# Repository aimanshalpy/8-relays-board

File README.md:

# 8 Relays Board
# 8 relays board with optocoupler protection for MCU 
# Donate by PayPal
## paypal.me/AymanShalaby

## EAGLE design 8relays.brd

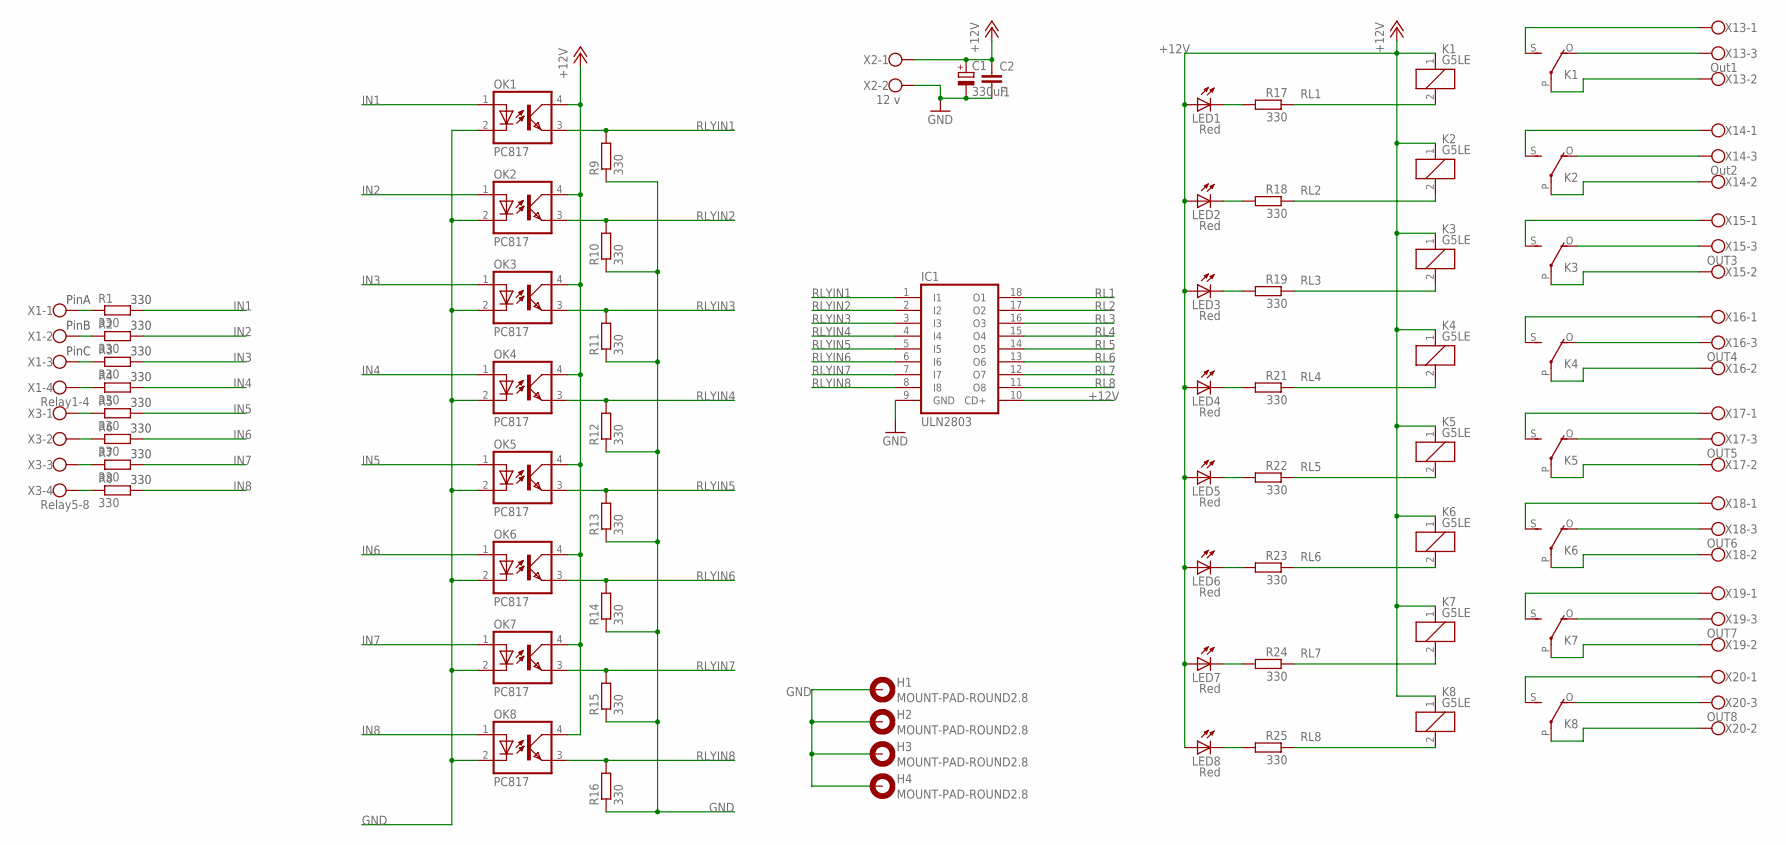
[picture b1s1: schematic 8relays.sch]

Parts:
C1: 330uF; E5-10,5
C2: .1; C5B2.5
H1, H2, H3, H4: MOUNT-PAD-ROUND2.8; 2,8-PAD
IC1: ULN2803; DIL18
K1, K2, K3, K4, K5, K6, K7, K8: G5LE
LED1, LED2, LED3, LED4, LED5, LED6, LED7, LED8: Red; LED3MM
OK1, OK2, OK3, OK4, OK5, OK6, OK7, OK8: PC817; DIL04
R1, R2, R3, R4, R5, R6, R7, R8, R9, R10, R11, R12, R13, R14, R15, R16, R17, R18, R19, R21, R22, R23, R24, R25: 330; 0204/5
X1: Relay1-4; W237-4
X2: 12 v; W237-102
X3: Relay5-8; W237-4
X13: Out1; W237-103
X14: Out2; W237-103
X15: OUT3; W237-103
X16: OUT4; W237-103
X17: OUT5; W237-103
X18: OUT6; W237-103
X19: OUT7; W237-103
X20: OUT8; W237-103

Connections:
+12V: C1.+, C2.1, IC1.10 (CD+), K1.1, K2.1, K3.1, K4.1, K5.1, K6.1, K7.1, K8.1, LED1.A, LED2.A, LED3.A, LED4.A, LED5.A, LED6.A, LED7.A, LED8.A, OK1.4 (COL), OK2.4 (COL), OK3.4 (COL), OK4.4 (COL), OK5.4 (COL), OK6.4 (COL), OK7.4 (COL), OK8.4 (COL), X2.1
GND: C1.-, C2.2, H1.B2,8, H2.B2,8, H3.B2,8, H4.B2,8, IC1.9 (GND), OK1.2 (C), OK2.2 (C), OK3.2 (C), OK4.2 (C), OK5.2 (C), OK6.2 (C), OK7.2 (C), OK8.2 (C), R9.1, R10.1, R11.1, R12.1, R13.1, R14.1, R15.1, R16.1, X2.2
IN1: OK1.1 (A), R1.2
IN2: OK2.1 (A), R2.2
IN3: OK3.1 (A), R3.2
IN4: OK4.1 (A), R4.2
IN5: OK5.1 (A), R5.2
IN6: OK6.1 (A), R6.2
IN7: OK7.1 (A), R7.2
IN8: OK8.1 (A), R8.2
unnamed: R1.1, X1.1
unnamed: LED5.K (C), R22.2
unnamed: K1.O, X13.3
unnamed: K1.P, X13.2
unnamed: R4.1, X1.4
unnamed: K1.S, X13.1
unnamed: R5.1, X3.1
unnamed: R6.1, X3.2
unnamed: R2.1, X1.2
unnamed: R3.1, X1.3
unnamed: K2.S, X14.1
unnamed: K2.O, X14.3
unnamed: K2.P, X14.2
unnamed: K3.S, X15.1
unnamed: K3.O, X15.3
unnamed: K3.P, X15.2
unnamed: K4.O, X16.3
unnamed: K5.O, X17.3
unnamed: K6.O, X18.3
unnamed: R7.1, X3.3
unnamed: LED1.K (C), R17.2
unnamed: K7.O, X19.3
unnamed: K8.O, X20.3
unnamed: R8.1, X3.4
unnamed: LED8.K (C), R25.2
unnamed: LED7.K (C), R24.2
unnamed: LED6.K (C), R23.2
unnamed: LED4.K (C), R21.2
unnamed: LED3.K (C), R19.2
unnamed: LED2.K (C), R18.2
unnamed: K8.P, X20.2
unnamed: K8.S, X20.1
unnamed: K7.P, X19.2
unnamed: K7.S, X19.1
unnamed: K6.P, X18.2
unnamed: K6.S, X18.1
unnamed: K5.P, X17.2
unnamed: K5.S, X17.1
unnamed: K4.P, X16.2
unnamed: K4.S, X16.1
RL1: IC1.18 (O1), K1.2, R17.1
RL2: IC1.17 (O2), K2.2, R18.1
RL3: IC1.16 (O3), K3.2, R19.1
RL4: IC1.15 (O4), K4.2, R21.1
RL5: IC1.14 (O5), K5.2, R22.1
RL6: IC1.13 (O6), K6.2, R23.1
RL7: IC1.12 (O7), K7.2, R24.1
RL8: IC1.11 (O8), K8.2, R25.1
RLYIN1: IC1.1 (I1), OK1.3 (EMIT), R9.2
RLYIN2: IC1.2 (I2), OK2.3 (EMIT), R10.2
RLYIN3: IC1.3 (I3), OK3.3 (EMIT), R11.2
RLYIN4: IC1.4 (I4), OK4.3 (EMIT), R12.2
RLYIN5: IC1.5 (I5), OK5.3 (EMIT), R13.2
RLYIN6: IC1.6 (I6), OK6.3 (EMIT), R14.2
RLYIN7: IC1.7 (I7), OK7.3 (EMIT), R15.2
RLYIN8: IC1.8 (I8), OK8.3 (EMIT), R16.2

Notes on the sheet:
PinA
PinB
PinC
330

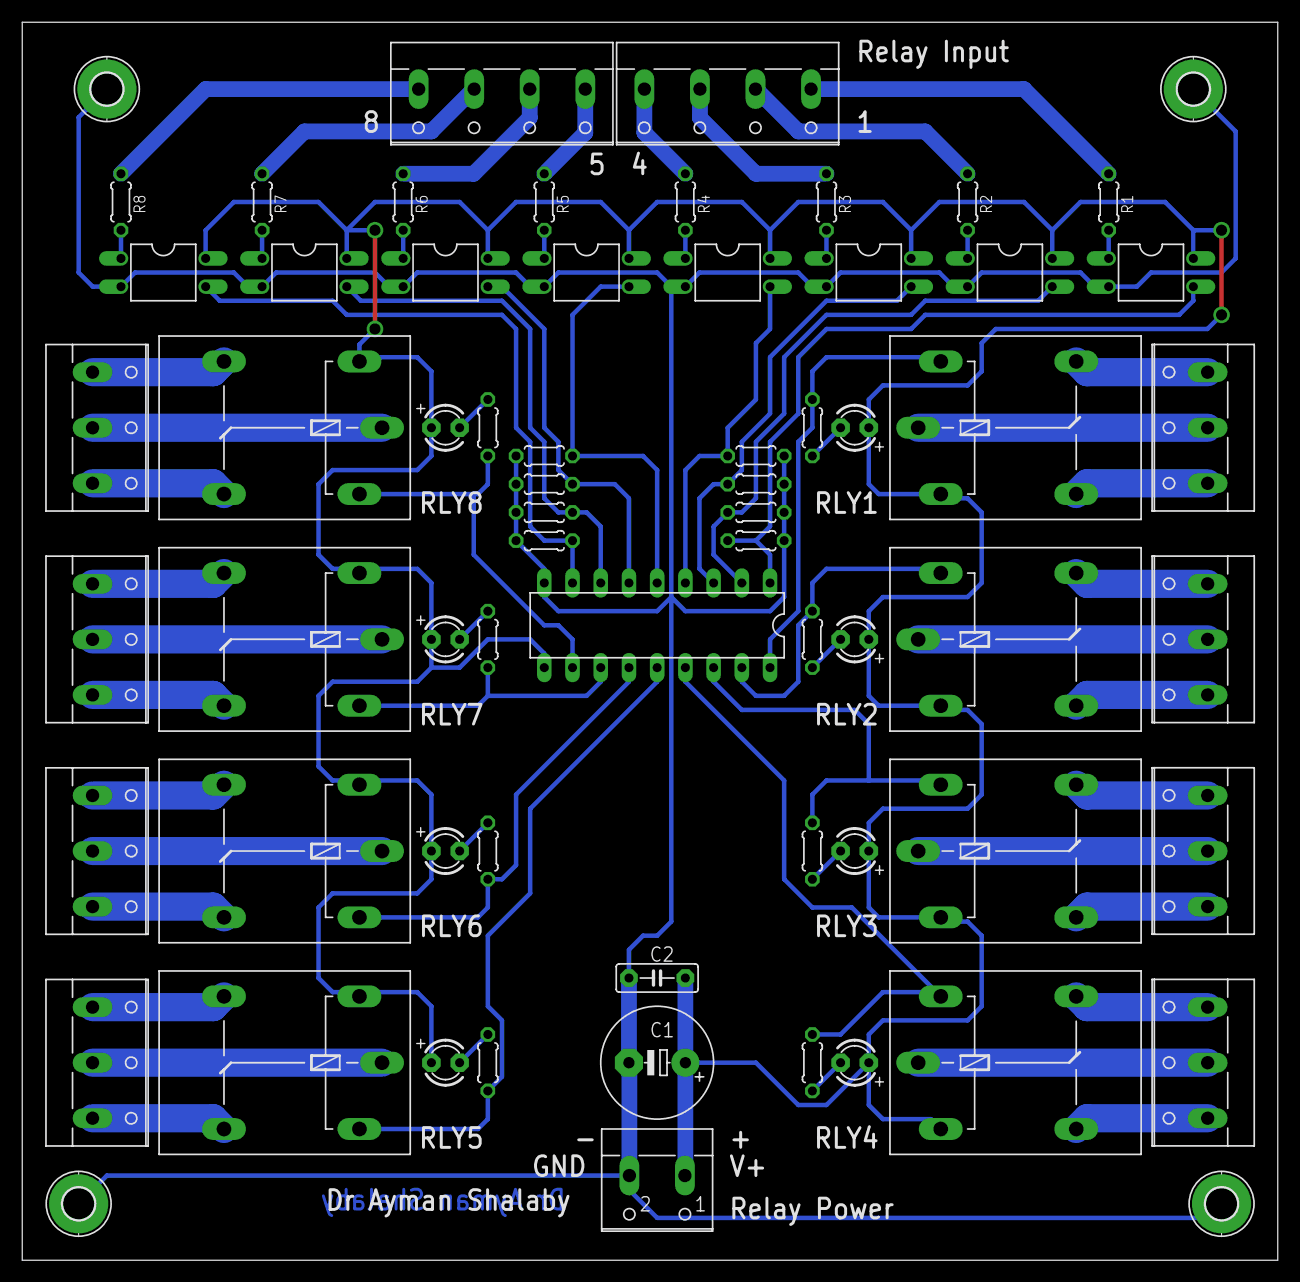
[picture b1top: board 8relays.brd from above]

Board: 2 copper layers, 113.0 x 111.4 mm, 66 parts (0 on the bottom side), 66 nets.

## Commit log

2018-02-16 8 Relays board for MCU
    Optocoupler protected 8 relays board for MCU use , Arduino, Rasp. Pi, STMs
2018-02-16 Update README.md
    8 Relays Board
